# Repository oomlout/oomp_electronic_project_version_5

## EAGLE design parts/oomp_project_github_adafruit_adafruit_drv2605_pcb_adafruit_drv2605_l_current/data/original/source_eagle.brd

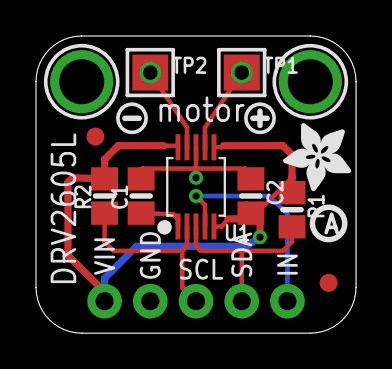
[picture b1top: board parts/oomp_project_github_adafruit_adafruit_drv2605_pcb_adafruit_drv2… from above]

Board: 2 copper layers, 17.8 x 16.5 mm, 16 parts (0 on the bottom side), 8 nets.

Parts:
C1, C2: 1uF; 0805-NO
FID1, FID2: FIDUCIAL""; FIDUCIAL_1MM
JP1: 1X05_ROUND_FULL_76
R1, R2: 10K; 0805-NO
TP1, TP2: TESTPOINT_PAD_2MM
U1: DRV2605LDGS; PSOP10
U$2, U$3: MOUNTINGHOLE2.5; MOUNTINGHOLE_2.5_PLATED
U$4: SYMBOL_PLUS
U$5: SYMBOL_MINUS
U$15: PCBFEAT-REV-040
U$18: ADAFRUIT_3.5MM

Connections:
GND: C1.1, C2.2, JP1.2, U1.8
IN/TRIG: JP1.5, U1.4
unnamed: C1.2, U1.1
OUT+: TP1.P$1, U1.7
OUT-: TP2.P$1, U1.9
SCL: JP1.3, R2.1, U1.2
SDA: JP1.4, R1.1, U1.3
VIN: C2.1, JP1.1, R1.2, R2.2, U1.5, U1.6, U1.10

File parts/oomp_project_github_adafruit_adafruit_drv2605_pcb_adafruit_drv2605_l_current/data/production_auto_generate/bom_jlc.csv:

Comment,Designator,Footprint,LCSC Part #
,JP1,Adafruit DRV2605L-import-fps:1X05_ROUND_FULL_76,C42431835
,U$18,Adafruit DRV2605L-import-fps:ADAFRUIT_3.5MM,
,U$15,Adafruit DRV2605L-import-fps:PCBFEAT-REV-040,
,U$5,Adafruit DRV2605L-import-fps:SYMBOL_MINUS,
,U$4,Adafruit DRV2605L-import-fps:SYMBOL_PLUS,
,"TP1,TP2",Adafruit DRV2605L-import-fps:TESTPOINT_PAD_2MM,
10K,"R1,R2",Adafruit DRV2605L-import-fps:0805-NO,C17414
1uF,"C1,C2",Adafruit DRV2605L-import-fps:0805-NO,
DRV2605LDGS,U1,Adafruit DRV2605L-import-fps:PSOP10,

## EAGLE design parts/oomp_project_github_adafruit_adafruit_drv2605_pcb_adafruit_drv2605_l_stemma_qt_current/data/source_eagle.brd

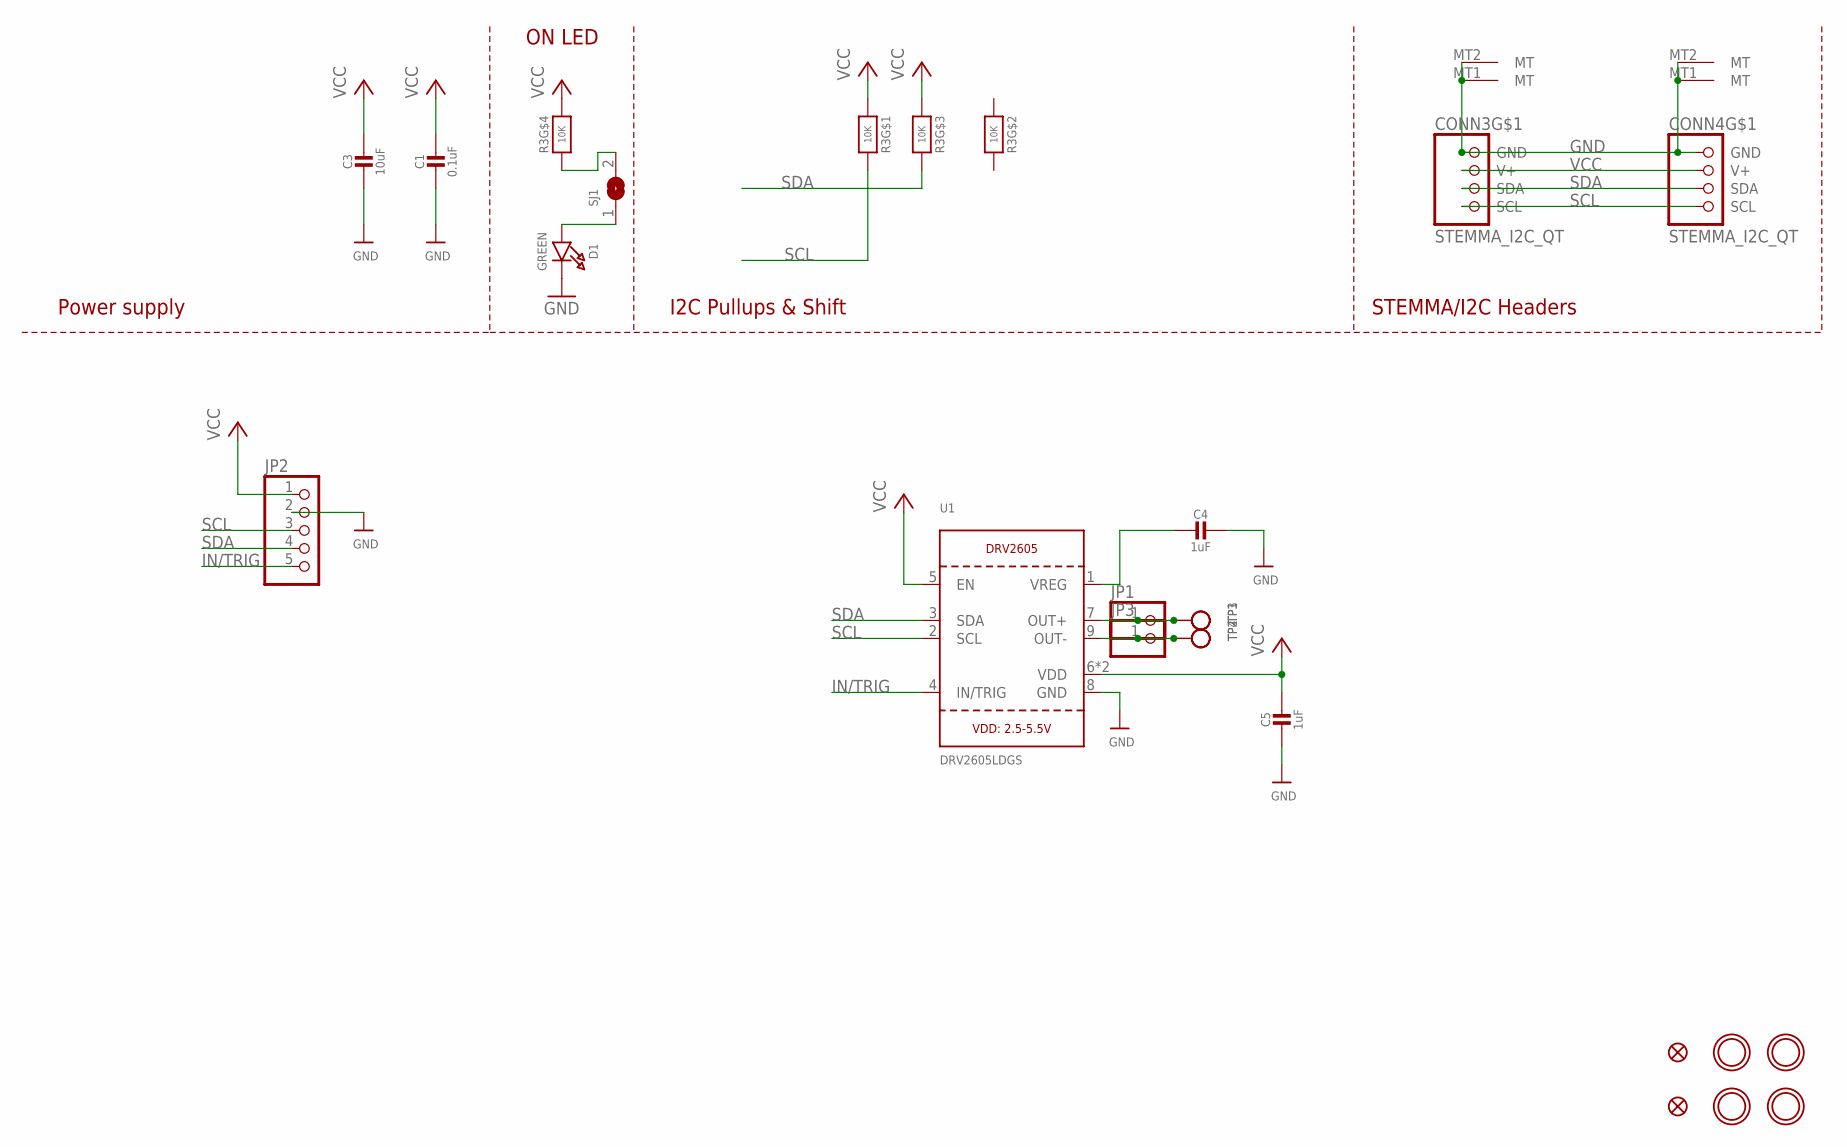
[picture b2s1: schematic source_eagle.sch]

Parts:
C1: 0.1uF; 0603-NO
C3: 10uF; 0805-NO
C4, C5: 1uF; 0603-NO
CONN3, CONN4: STEMMA_I2C_QT; JST_SH4
D1: GREEN; CHIPLED_0603_NOOUTLINE
FID3, FID4: FIDUCIAL_1MM
JP1, JP3: HEADER-1X1; 1X01_OVAL
JP2: HEADER-1X576MIL; 1X05_ROUND_76
R3: 10K; RESPACK_4X0603
SJ1: SOLDERJUMPERCLOSED; SOLDERJUMPER_CLOSEDWIRE
TP1, TP2, TP3, TP4: TESTPOINTPAD2MM; TESTPOINT_PAD_2MM
U1: DRV2605LDGS; PSOP10
U$1, U$17, U$19, U$21: MOUNTINGHOLE2.5; MOUNTINGHOLE_2.5_PLATED

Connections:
GND: C1.2, C3.2, C4.1, C5.2, CONN3.1 (GND), CONN3.MT1 (MT), CONN3.MT2 (MT), CONN4.1 (GND), CONN4.MT1 (MT), CONN4.MT2 (MT), D1.C, JP2.2, U1.8 (GND)
IN/TRIG: JP2.5, U1.4 (IN/TRIG)
unnamed: R3.4 (1), SJ1.2
unnamed: D1.A, SJ1.1
unnamed: C4.2, U1.1 (VREG)
OUT+: JP1.1, TP1.P$1, TP3.P$1, U1.7 (OUT+)
OUT-: JP3.1, TP2.P$1, TP4.P$1, U1.9 (OUT-)
SCL: CONN3.4 (SCL), CONN4.4 (SCL), JP2.3, R3.8 (2), U1.2 (SCL)
SDA: CONN3.3 (SDA), CONN4.3 (SDA), JP2.4, R3.6 (2), U1.3 (SDA)
VCC: C1.1, C3.1, C5.1, CONN3.2 (V+), CONN4.2 (V+), JP2.1, R3.1, R3.3 (1), R3.5 (2), U1.5 (EN), U1.6 (VDD), U1.10 (VDD)

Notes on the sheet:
I2C Pullups & Shift
STEMMA/I2C Headers
ON LED
Power supply

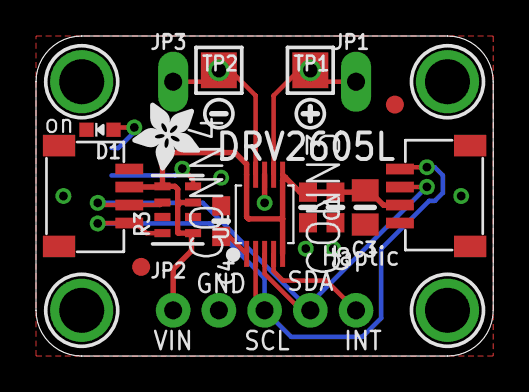
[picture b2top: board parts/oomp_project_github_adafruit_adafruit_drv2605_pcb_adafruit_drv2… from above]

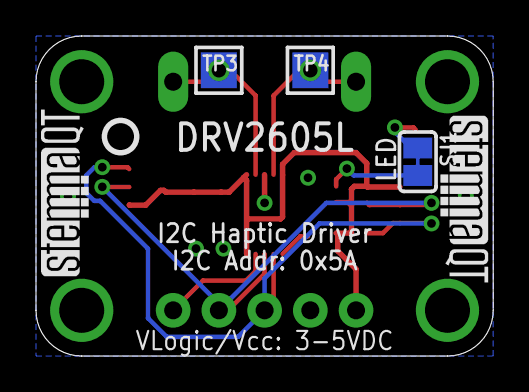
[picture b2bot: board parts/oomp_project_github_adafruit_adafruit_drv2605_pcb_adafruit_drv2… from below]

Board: 2 copper layers, 25.4 x 17.8 mm, 29 parts (6 on the bottom side), 10 nets.

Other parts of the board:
U$2: SYMBOL_PLUS
U$3: SYMBOL_MINUS
U$22: ADAFRUIT_3.5MM
U$25: PCBFEAT-REV-040
U$30, U$31: STEMMAQT

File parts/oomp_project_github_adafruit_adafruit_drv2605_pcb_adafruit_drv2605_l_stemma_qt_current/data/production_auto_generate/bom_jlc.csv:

Comment,Designator,Footprint,LCSC Part #
,"JP1,JP3",Adafruit DRV2605L STEMMA QT-import-fps:1X01_OVAL,C7501259
,JP2,Adafruit DRV2605L STEMMA QT-import-fps:1X05_ROUND_76,C42431835
,U$22,Adafruit DRV2605L STEMMA QT-import-fps:ADAFRUIT_3.5MM,
,U$25,Adafruit DRV2605L STEMMA QT-import-fps:PCBFEAT-REV-040,
,"U$30,U$31",Adafruit DRV2605L STEMMA QT-import-fps:STEMMAQT,
,U$3,Adafruit DRV2605L STEMMA QT-import-fps:SYMBOL_MINUS,
,U$2,Adafruit DRV2605L STEMMA QT-import-fps:SYMBOL_PLUS,
,"TP1,TP2,TP3,TP4",Adafruit DRV2605L STEMMA QT-import-fps:TESTPOINT_PAD_2MM,
0.1uF,C1,Adafruit DRV2605L STEMMA QT-import-fps:0603-NO,C14663
10K,R3,Adafruit DRV2605L STEMMA QT-import-fps:RESPACK_4X0603,C98220
10uF,C3,Adafruit DRV2605L STEMMA QT-import-fps:0805-NO,
1uF,"C4,C5",Adafruit DRV2605L STEMMA QT-import-fps:0603-NO,C5673
DRV2605LDGS,U1,Adafruit DRV2605L STEMMA QT-import-fps:PSOP10,
GREEN,D1,Adafruit DRV2605L STEMMA QT-import-fps:CHIPLED_0603_NOOUTLINE,
STEMMA_I2C_QT,"CONN3,CONN4",Adafruit DRV2605L STEMMA QT-import-fps:JST_SH4,C160404

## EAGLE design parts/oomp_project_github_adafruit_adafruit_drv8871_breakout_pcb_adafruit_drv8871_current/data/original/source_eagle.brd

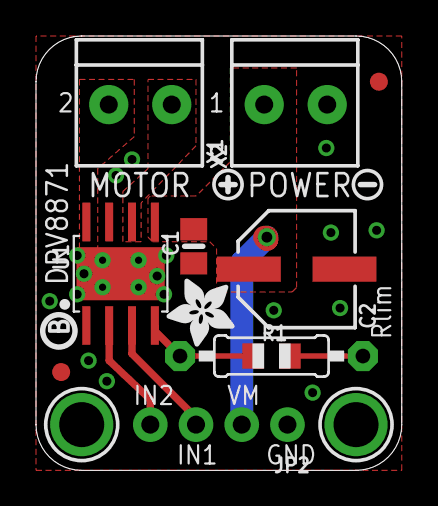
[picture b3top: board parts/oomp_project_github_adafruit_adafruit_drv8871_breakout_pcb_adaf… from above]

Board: 2 copper layers, 20.3 x 24.1 mm, 15 parts (0 on the bottom side), 7 nets.

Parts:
C1: 0.1uF/50V; 0805-NO
C2: 22uF/63V; PANASONIC_D
FID1, FID2: FIDUCIAL""; FIDUCIAL_1MM
JP2: 1X04_ROUND_76
R1: 30K; 0805-THM
U1: DRV8871; HSOP8
U$9, U$10: MOUNTINGHOLE2.5; MOUNTINGHOLE_2.5_PLATED
U$11: SYMBOL_PLUS
U$12: SYMBOL_MINUS
U$14: ADAFRUIT_3.5MM
U$15: PCBFEAT-REV-040
X1: DCMOTOR; TERMBLOCK_1X2-3.5MM
X2: POWER; TERMBLOCK_1X2-3.5MM

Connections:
GND: C1.2, C2.-, JP2.1, R1.1, U1.1, U1.7, U1.GND, U1.P$1, U1.P$2, U1.P$3, U1.P$4, X2.2
IN1: JP2.3, U1.3
IN2: JP2.4, U1.2
unnamed: R1.2, U1.4
OUT1: U1.6, X1.2
OUT2: U1.8, X1.1
VMOTOR: C1.1, C2.+, JP2.2, U1.5, X2.1

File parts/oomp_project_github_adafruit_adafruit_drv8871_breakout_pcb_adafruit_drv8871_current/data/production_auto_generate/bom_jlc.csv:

Comment,Designator,Footprint,LCSC Part #
,JP2,Adafruit DRV8871-import-fps:1X04_ROUND_76,C42431795
,U$14,Adafruit DRV8871-import-fps:ADAFRUIT_3.5MM,
,U$15,Adafruit DRV8871-import-fps:PCBFEAT-REV-040,
,U$12,Adafruit DRV8871-import-fps:SYMBOL_MINUS,
,U$11,Adafruit DRV8871-import-fps:SYMBOL_PLUS,
0.1uF/50V,C1,Adafruit DRV8871-import-fps:0805-NO,
22uF/63V,C2,Adafruit DRV8871-import-fps:PANASONIC_D,
30K,R1,Adafruit DRV8871-import-fps:0805-THM,
DCMOTOR,X1,Adafruit DRV8871-import-fps:TERMBLOCK_1X2-3.5MM,
DRV8871,U1,Adafruit DRV8871-import-fps:HSOP8,
POWER,X2,Adafruit DRV8871-import-fps:TERMBLOCK_1X2-3.5MM,

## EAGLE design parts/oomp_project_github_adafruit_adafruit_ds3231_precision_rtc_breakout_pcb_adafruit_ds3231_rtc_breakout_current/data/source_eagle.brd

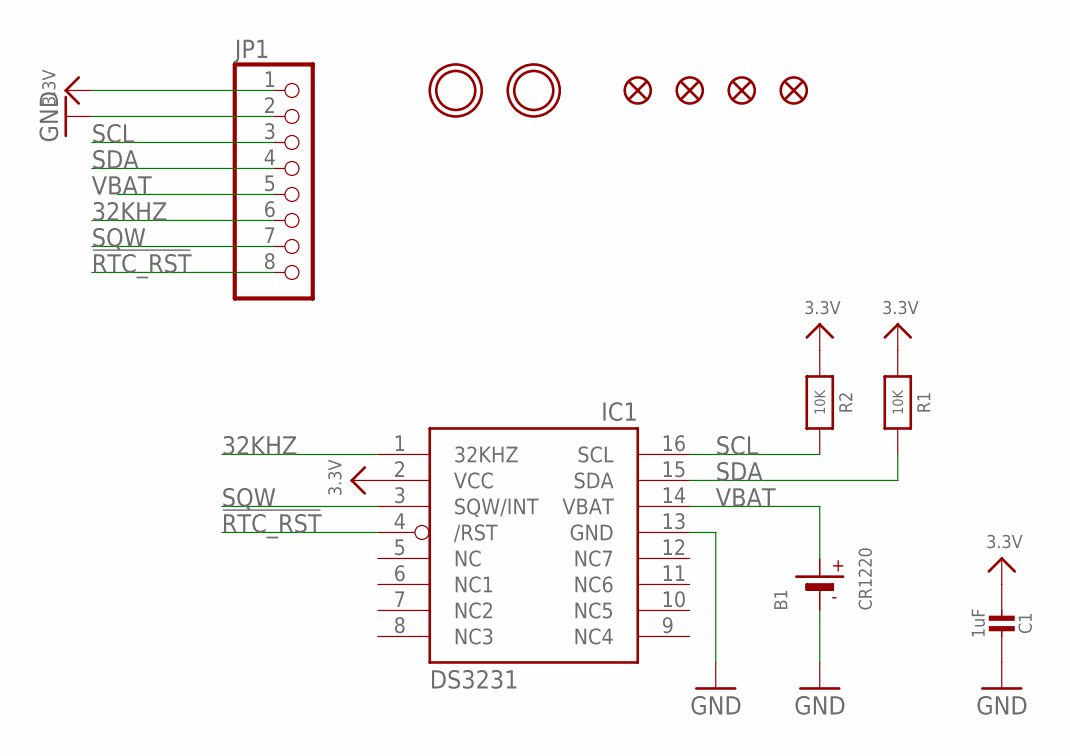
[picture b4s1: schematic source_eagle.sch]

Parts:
B1: CR1220
C1: 1uF; 0805-NO
FID1, FID2, FID3, FID4: FIDUCIAL""; FIDUCIAL_1MM
IC1: DS3231/SO; SO16W
JP1: HEADER-1X870MIL; 1X08_ROUND_70
R1, R2: 10K; 0805-NO
U$6, U$7: MOUNTINGHOLE2.5; MOUNTINGHOLE_2.5_PLATED

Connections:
3.3V: C1.2, IC1.2 (VCC), JP1.1, R1.1, R2.1
32KHZ: IC1.1 (32KHZ), JP1.6
!RTC_RST: IC1.4 (/RST), JP1.8
GND: B1.-, C1.1, IC1.13 (GND), JP1.2
SCL: IC1.16 (SCL), JP1.3, R2.2
SDA: IC1.15 (SDA), JP1.4, R1.2
SQW: IC1.3 (SQW/INT), JP1.7
VBAT: B1.+$1 (+), IC1.14 (VBAT), JP1.5

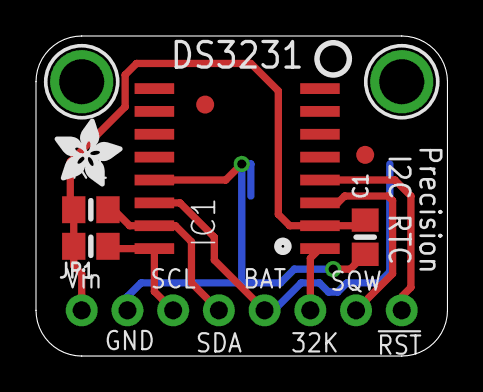
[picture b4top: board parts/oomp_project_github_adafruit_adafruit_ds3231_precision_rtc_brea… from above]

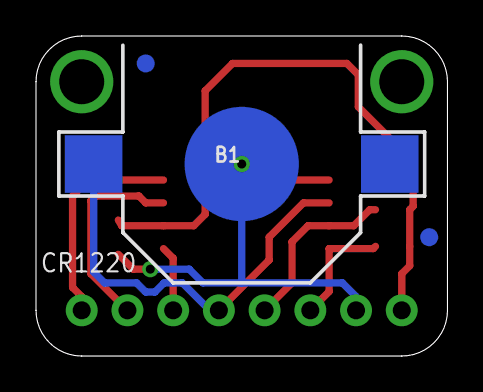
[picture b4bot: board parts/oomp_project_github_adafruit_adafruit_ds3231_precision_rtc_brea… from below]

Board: 2 copper layers, 22.9 x 17.8 mm, 14 parts (3 on the bottom side), 8 nets.

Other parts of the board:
U$8: ADAFRUIT_3.5MM
U$9: PCBFEAT-REV-040

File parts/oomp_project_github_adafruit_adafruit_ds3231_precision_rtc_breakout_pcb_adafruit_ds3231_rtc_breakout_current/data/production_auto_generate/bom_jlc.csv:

Comment,Designator,Footprint,LCSC Part #
,JP1,Adafruit DS3231 RTC Breakout-import-fps:1X08_ROUND_70,C492421
,U$8,Adafruit DS3231 RTC Breakout-import-fps:ADAFRUIT_3.5MM,
,U$9,Adafruit DS3231 RTC Breakout-import-fps:PCBFEAT-REV-040,
10K,"R1,R2",Adafruit DS3231 RTC Breakout-import-fps:0805-NO,C17414
1uF,C1,Adafruit DS3231 RTC Breakout-import-fps:0805-NO,
CR1220,B1,Adafruit DS3231 RTC Breakout-import-fps:CR1220,
DS3231/SO,IC1,Adafruit DS3231 RTC Breakout-import-fps:SO16W,

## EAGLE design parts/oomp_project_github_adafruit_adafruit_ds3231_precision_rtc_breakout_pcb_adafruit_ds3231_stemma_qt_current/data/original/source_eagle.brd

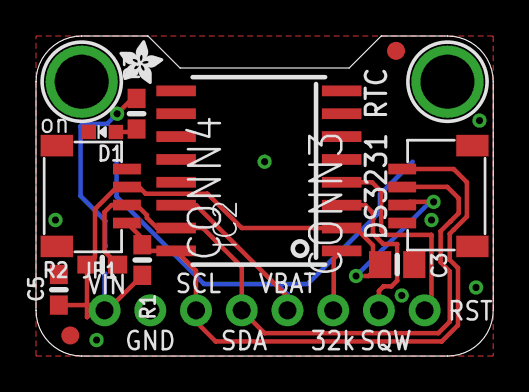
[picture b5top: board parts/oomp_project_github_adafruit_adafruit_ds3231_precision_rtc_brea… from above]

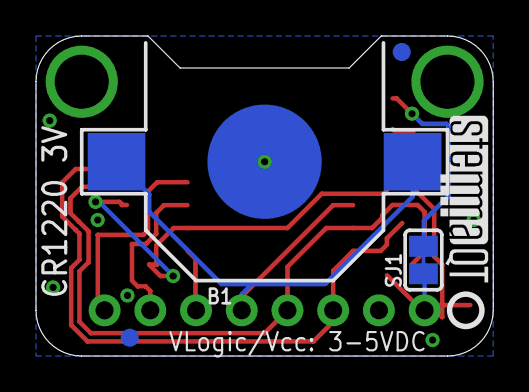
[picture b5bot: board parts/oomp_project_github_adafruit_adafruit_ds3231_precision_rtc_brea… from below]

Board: 2 copper layers, 25.4 x 17.8 mm, 21 parts (6 on the bottom side), 10 nets.

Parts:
B1: CR1220
C3: 10uF; 0805-NO
C5: 0.1uF; 0603-NO
CONN3, CONN4: STEMMA_I2C_QT; JST_SH4
D1: GREEN; CHIPLED_0603_NOOUTLINE
FID1, FID2, FID3, FID4: FIDUCIAL_1MM
IC2: DS3231/SO; SO16W
JP1: 1X08_ROUND_70
R1, R2, R3: 10k; 0603-NO
SJ1: SOLDERJUMPER_CLOSEDWIRE
U$1: ADAFRUIT_2.5MM
U$9, U$17: MOUNTINGHOLE3.0THIN; MOUNTINGHOLE_3.0_PLATEDTHIN
U$25: PCBFEAT-REV-040
U$31: STEMMAQT

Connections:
32KHZ: IC2.1, JP1.6
!RTC_RST: IC2.4, JP1.8
GND: B1.-, C3.2, C5.2, CONN3.1, CONN3.MT1, CONN3.MT2, CONN4.1, CONN4.MT1, CONN4.MT2, D1.C, IC2.5, IC2.6, IC2.7, IC2.8, IC2.9, IC2.10, IC2.11, IC2.12, IC2.13, JP1.2
unnamed: R3.2, SJ1.2
unnamed: D1.A, R3.1
SCL: CONN3.4, CONN4.4, IC2.16, JP1.3, R1.1
SDA: CONN3.3, CONN4.3, IC2.15, JP1.4, R2.1
SQW: IC2.3, JP1.7
VBAT: B1.+$1, B1.+$2, IC2.14, JP1.5
VCC: C3.1, C5.1, CONN3.2, CONN4.2, IC2.2, JP1.1, R1.2, R2.2, SJ1.1

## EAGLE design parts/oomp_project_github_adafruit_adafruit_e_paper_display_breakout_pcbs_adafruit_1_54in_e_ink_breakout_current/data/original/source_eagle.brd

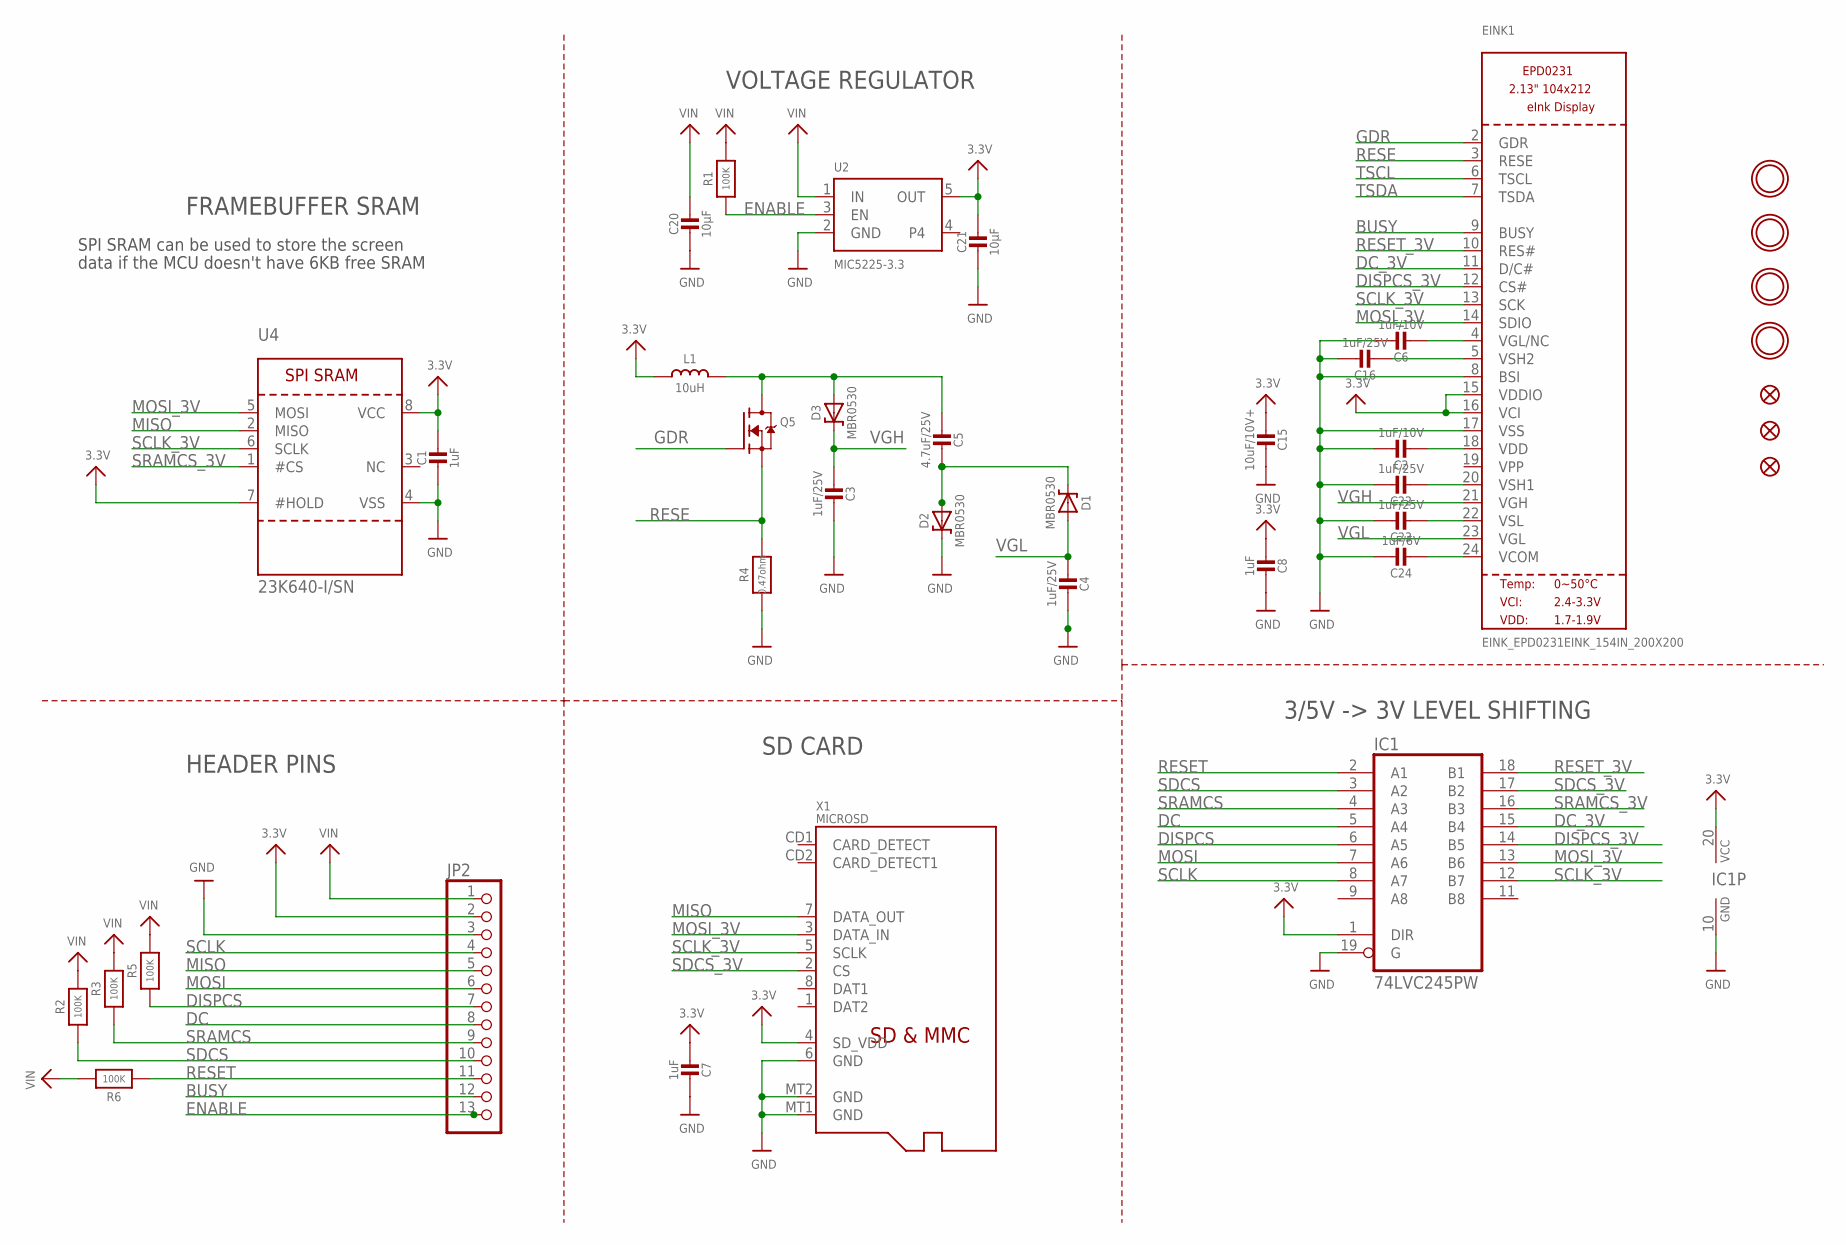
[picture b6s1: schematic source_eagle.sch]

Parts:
C1: 1uF; 0805_10MGAP
C2, C6: 1uF/10V; 0805-NO
C3, C4, C16, C22, C23: 1uF/25V; 0805-NO
C5: 4.7uF/25V; 0805-NO
C7, C8: 1uF; 0805-NO
C15: 10uF/10V+; 0805-NO
C20, C21: 10µF; 0805-NO
C24: 1uF/6V; 0805-NO
D1, D2, D3: MBR0530; SOD-123
EINK1: EINK_EPD0231EINK_154IN_200X200; EINK_154IN
FID1, FID2, FID3: FIDUCIAL_1MM
IC1: 74LVC245PW; TSSOP20
JP2: HEADER-1X13; 1X13_ROUND_70
L1: 10uH; INDUCTOR_4X4MM_NR401
Q5: IRLML0100; SOT23-3
R1, R2, R3, R5, R6: 100K; 0805-NO
R4: 0.47ohm; 0805_10MGAP
U2: MIC5225-3.3; SOT23-5
U4: 23K640-I/SN; SOIC8_150MIL
U$3, U$4, U$5, U$6: MOUNTINGHOLE2.5; MOUNTINGHOLE_2.5_PLATED
X1: MICROSD

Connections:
3.3V: C1.1, C7.1, C8.1, C15.2, C21.1, EINK1.15 (VDDIO), EINK1.16 (VCI), IC1.1 (DIR), IC1.20 (VCC), JP2.2, L1.P$2 (2), U2.5 (OUT), U4.7 (#HOLD), U4.8 (VCC), X1.4 (SD_VDD)
BUSY: EINK1.9 (BUSY), JP2.12
DC: IC1.5 (A4), JP2.8
DC_3V: EINK1.11 (D/C#), IC1.15 (B4)
DISPCS: IC1.6 (A5), JP2.7, R5.1
DISPCS_3V: EINK1.12 (CS#), IC1.14 (B5)
ENABLE: JP2.13, R1.1, U2.3 (EN)
GDR: EINK1.2 (GDR), Q5.1 (G)
GND: C1.2, C2.1, C3.2, C4.2, C6.1, C7.2, C8.2, C15.1, C16.1, C20.2, C21.2, C22.1, C23.1, C24.1, D2.C, EINK1.8 (BSI), EINK1.17 (VSS), IC1.10 (GND), IC1.19 (G), JP2.3, R4.2, U2.2 (GND), U4.4 (VSS), X1.6 (GND), X1.MT1 (GND), X1.MT2 (GND)
MISO: JP2.5, U4.2 (MISO), X1.7 (DATA_OUT)
MOSI: IC1.7 (A6), JP2.6
MOSI_3V: EINK1.14 (SDIO), IC1.13 (B6), U4.5 (MOSI), X1.3 (DATA_IN)
unnamed: C5.2, D1.C, D2.A
unnamed: C5.1, D3.A, L1.P$1 (1), Q5.3 (D)
unnamed: C16.2, EINK1.5 (VSH2)
unnamed: C2.2, EINK1.18 (VDD)
unnamed: C22.2, EINK1.20 (VSH1)
unnamed: C6.2, EINK1.4 (VGL/NC)
unnamed: C23.2, EINK1.22 (VSL)
unnamed: C24.2, EINK1.24 (VCOM)
RESE: EINK1.3 (RESE), Q5.2 (S), R4.1
RESET: IC1.2 (A1), JP2.11, R6.1
RESET_3V: EINK1.10 (RES#), IC1.18 (B1)
SCLK: IC1.8 (A7), JP2.4
SCLK_3V: EINK1.13 (SCK), IC1.12 (B7), U4.6 (SCLK), X1.5 (SCLK)
SDCS: IC1.3 (A2), JP2.10, R2.1
SDCS_3V: IC1.17 (B2), X1.2 (CS)
SRAMCS: IC1.4 (A3), JP2.9, R3.1
SRAMCS_3V: IC1.16 (B3), U4.1 (#CS)
TSCL: EINK1.6 (TSCL)
TSDA: EINK1.7 (TSDA)
VGH: C3.1, D3.C, EINK1.21 (VGH)
VGL: C4.1, D1.A, EINK1.23 (VGL)
VIN: C20.1, JP2.1, R1.2, R2.2, R3.2, R5.2, R6.2, U2.1 (IN)

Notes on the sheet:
VOLTAGE REGULATOR
3/5V -> 3V LEVEL SHIFTING
HEADER PINS
FRAMEBUFFER SRAM
SPI SRAM can be used to store the screen
data if the MCU doesn't have 6KB free SRAM
SD CARD

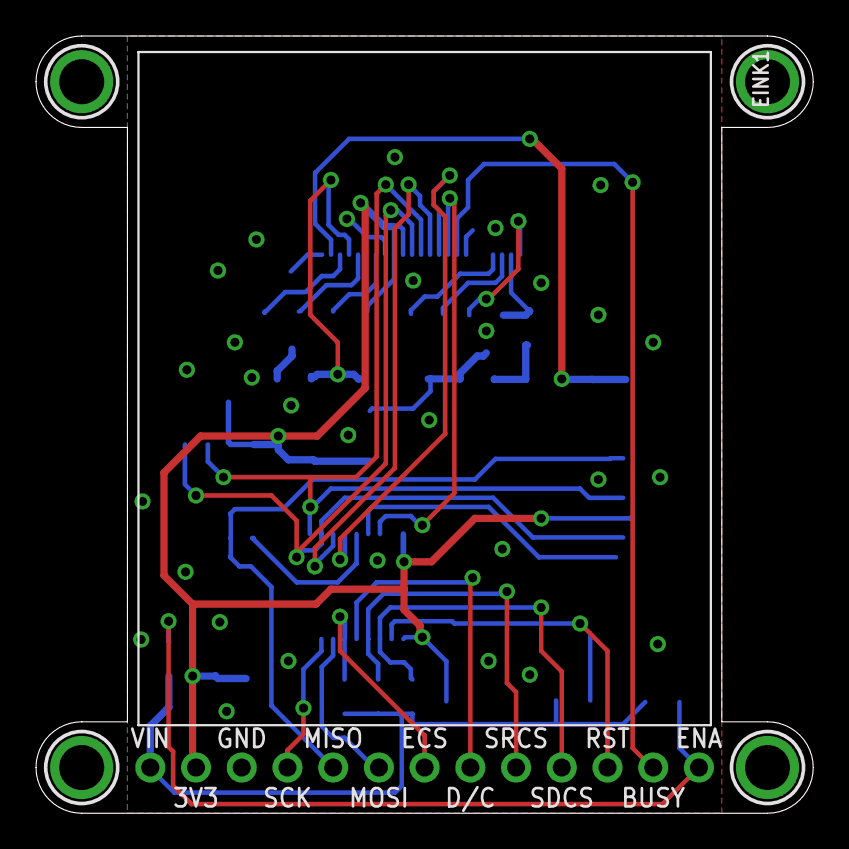
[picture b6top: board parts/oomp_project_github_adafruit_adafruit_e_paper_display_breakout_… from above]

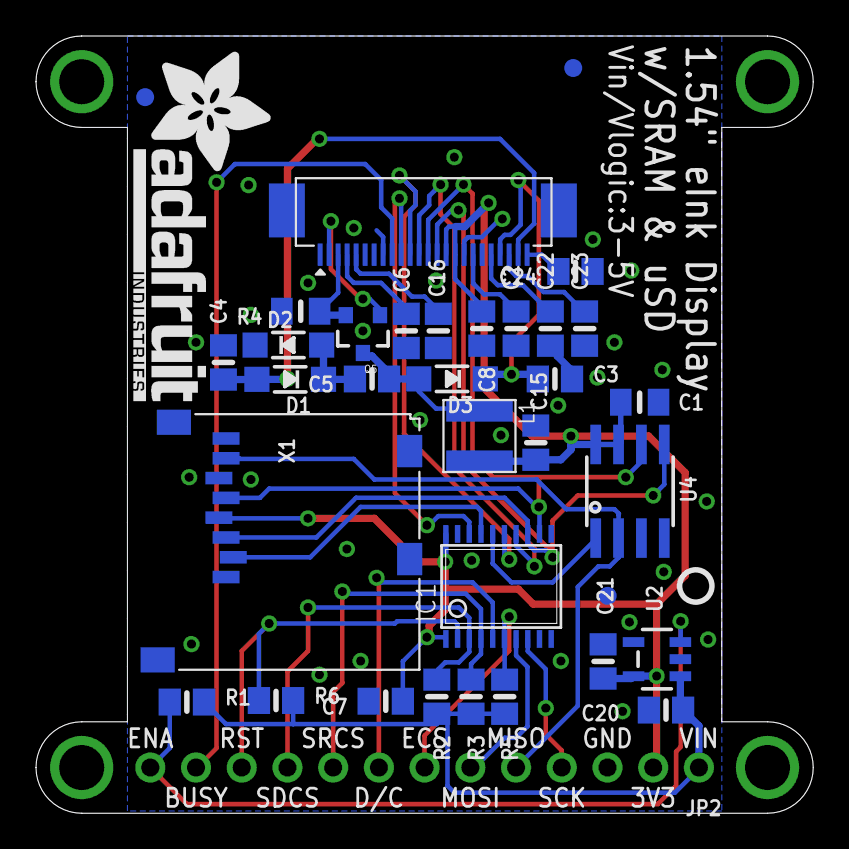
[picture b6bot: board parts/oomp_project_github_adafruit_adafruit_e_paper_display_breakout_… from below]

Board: 2 copper layers, 43.2 x 43.2 mm, 41 parts (36 on the bottom side), 32 nets.

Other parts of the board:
U$9: PCBFEAT-REV-040
U$28: ADAFRUIT_TEXT_20MM

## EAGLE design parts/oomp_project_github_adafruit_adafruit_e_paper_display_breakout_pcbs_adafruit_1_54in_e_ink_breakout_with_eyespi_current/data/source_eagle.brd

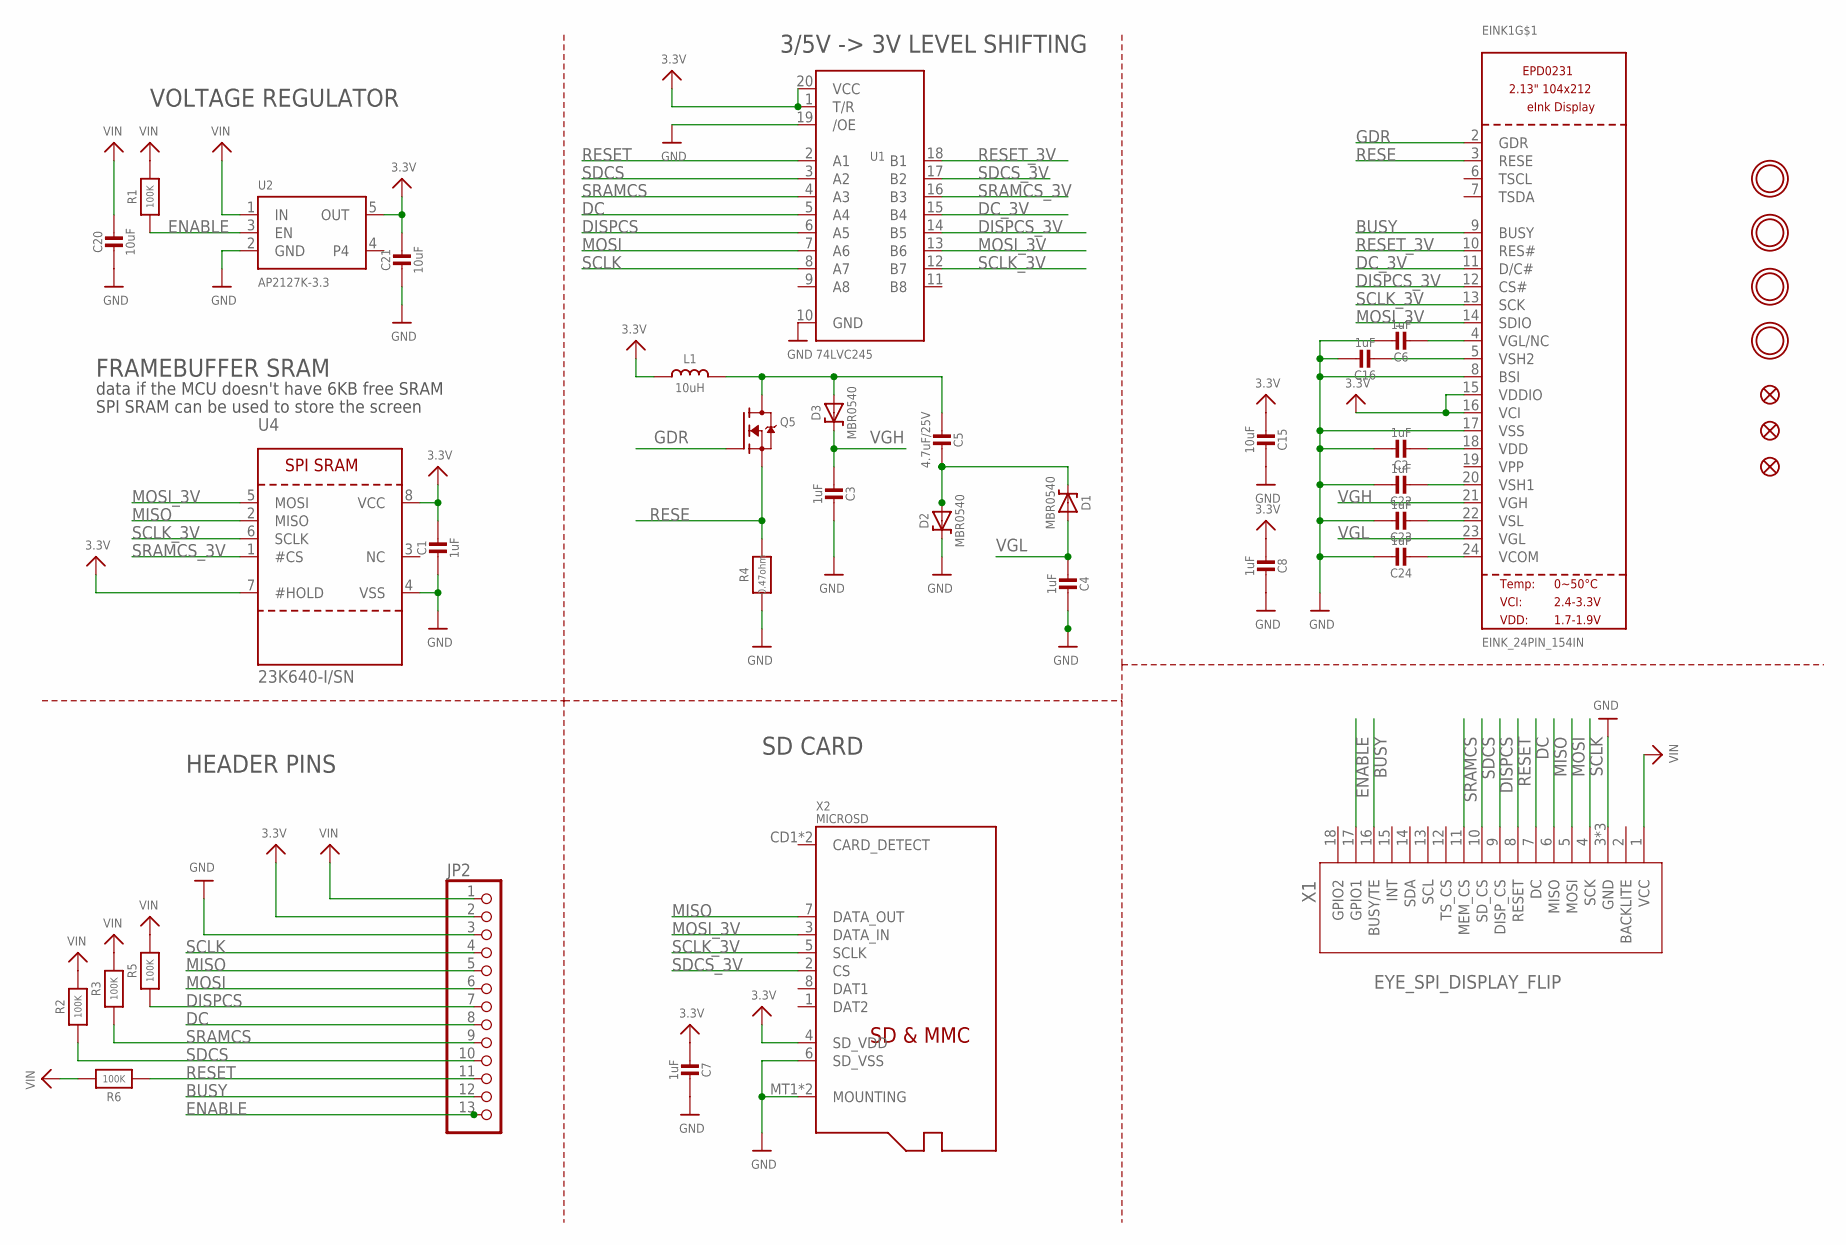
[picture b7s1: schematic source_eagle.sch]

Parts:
C1, C2, C3, C4, C6, C7, C8, C16, C22, C23, C24: 1uF; 0805-NO
C5: 4.7uF/25V; 0805-NO
C15, C20, C21: 10uF; 0805-NO
D1, D2, D3: MBR0540; SOD-123
EINK1: EINK_24PIN_154IN; EINK_154IN
FID1, FID2, FID3: FIDUCIAL_1MM
JP2: HEADER-1X13; 1X13_ROUND_70
L1: 10uH; INDUCTOR_4X4MM_NR401
Q5: IRLML0100; SOT23-3
R1, R2, R3, R5, R6: 100K; 0805-NO
R4: 0.47ohm; 0805_10MGAP
U1: 74LVC245; TSSOP20
U2: AP2127K-3.3; SOT23-5
U4: 23K640-I/SN; SOIC8_150MIL
U$3, U$4, U$5, U$6: MOUNTINGHOLE2.5; MOUNTINGHOLE_2.5_PLATED
X1: EYE_SPI_DISPLAY_FLIP; EYE_SPI_DISPLAY_BOTCONTACT
X2: MICROSD

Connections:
3.3V: C1.1, C7.1, C8.1, C15.2, C21.1, EINK1.15 (VDDIO), EINK1.16 (VCI), JP2.2, L1.P$2 (2), U1.1 (T/R), U1.20 (VCC), U2.5 (OUT), U4.7 (#HOLD), U4.8 (VCC), X2.4 (SD_VDD)
BUSY: EINK1.9 (BUSY), JP2.12, X1.16 (BUSY/TE)
DC: JP2.8, U1.5 (A4), X1.7 (DC)
DC_3V: EINK1.11 (D/C#), U1.15 (B4)
DISPCS: JP2.7, R5.1, U1.6 (A5), X1.9 (DISP_CS)
DISPCS_3V: EINK1.12 (CS#), U1.14 (B5)
ENABLE: JP2.13, R1.1, U2.3 (EN), X1.17 (GPIO1)
GDR: EINK1.2 (GDR), Q5.1 (G)
GND: C1.2, C2.1, C3.2, C4.2, C6.1, C7.2, C8.2, C15.1, C16.1, C20.2, C21.2, C22.1, C23.1, C24.1, D2.C, EINK1.8 (BSI), EINK1.17 (VSS), JP2.3, R4.2, U1.10 (GND), U1.19 (/OE), U2.2 (GND), U4.4 (VSS), X1.3 (GND), X1.SUPPORT1 (GND), X1.SUPPORT2 (GND), X2.6 (SD_VSS), X2.MT1 (MOUNTING), X2.MT2 (MOUNTING)
MISO: JP2.5, U4.2 (MISO), X1.6 (MISO), X2.7 (DATA_OUT)
MOSI: JP2.6, U1.7 (A6), X1.5 (MOSI)
MOSI_3V: EINK1.14 (SDIO), U1.13 (B6), U4.5 (MOSI), X2.3 (DATA_IN)
unnamed: C5.2, D1.C, D2.A
unnamed: C5.1, D3.A, L1.P$1 (1), Q5.3 (D)
unnamed: C16.2, EINK1.5 (VSH2)
unnamed: C2.2, EINK1.18 (VDD)
unnamed: C22.2, EINK1.20 (VSH1)
unnamed: C6.2, EINK1.4 (VGL/NC)
unnamed: C23.2, EINK1.22 (VSL)
unnamed: C24.2, EINK1.24 (VCOM)
RESE: EINK1.3 (RESE), Q5.2 (S), R4.1
RESET: JP2.11, R6.1, U1.2 (A1), X1.8 (RESET)
RESET_3V: EINK1.10 (RES#), U1.18 (B1)
SCLK: JP2.4, U1.8 (A7), X1.4 (SCK)
SCLK_3V: EINK1.13 (SCK), U1.12 (B7), U4.6 (SCLK), X2.5 (SCLK)
SDCS: JP2.10, R2.1, U1.3 (A2), X1.10 (SD_CS)
SDCS_3V: U1.17 (B2), X2.2 (CS)
SRAMCS: JP2.9, R3.1, U1.4 (A3), X1.11 (MEM_CS)
SRAMCS_3V: U1.16 (B3), U4.1 (#CS)
VGH: C3.1, D3.C, EINK1.21 (VGH)
VGL: C4.1, D1.A, EINK1.23 (VGL)
VIN: C20.1, JP2.1, R1.2, R2.2, R3.2, R5.2, R6.2, U2.1 (IN), X1.1 (VCC)

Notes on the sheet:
VOLTAGE REGULATOR
3/5V -> 3V LEVEL SHIFTING
HEADER PINS
FRAMEBUFFER SRAM
SPI SRAM can be used to store the screen
data if the MCU doesn't have 6KB free SRAM
SD CARD

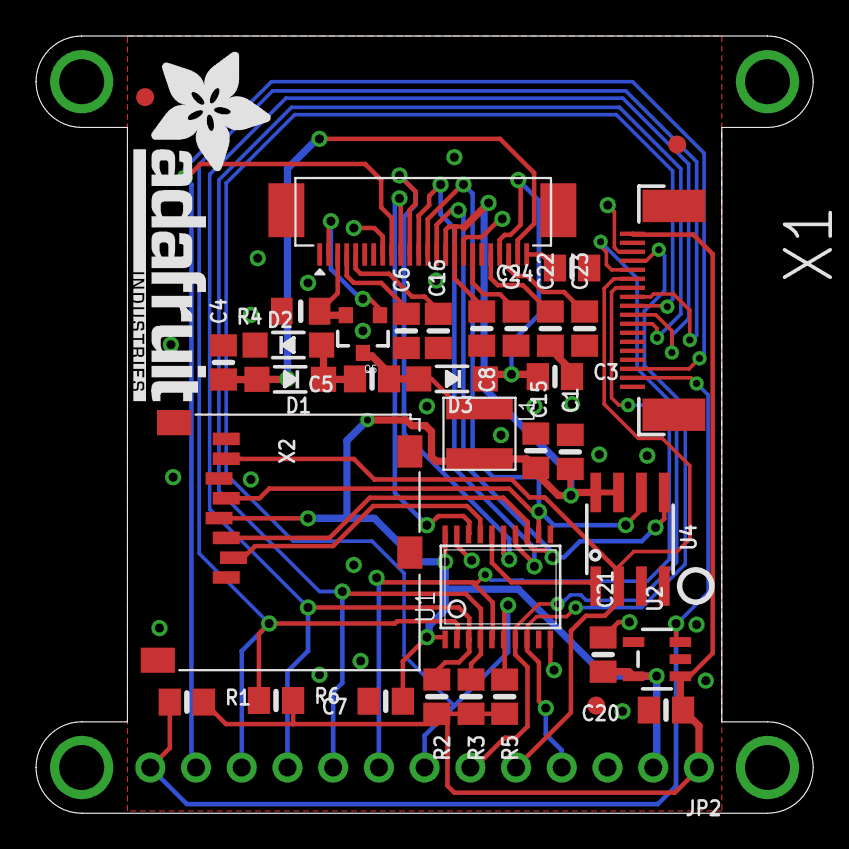
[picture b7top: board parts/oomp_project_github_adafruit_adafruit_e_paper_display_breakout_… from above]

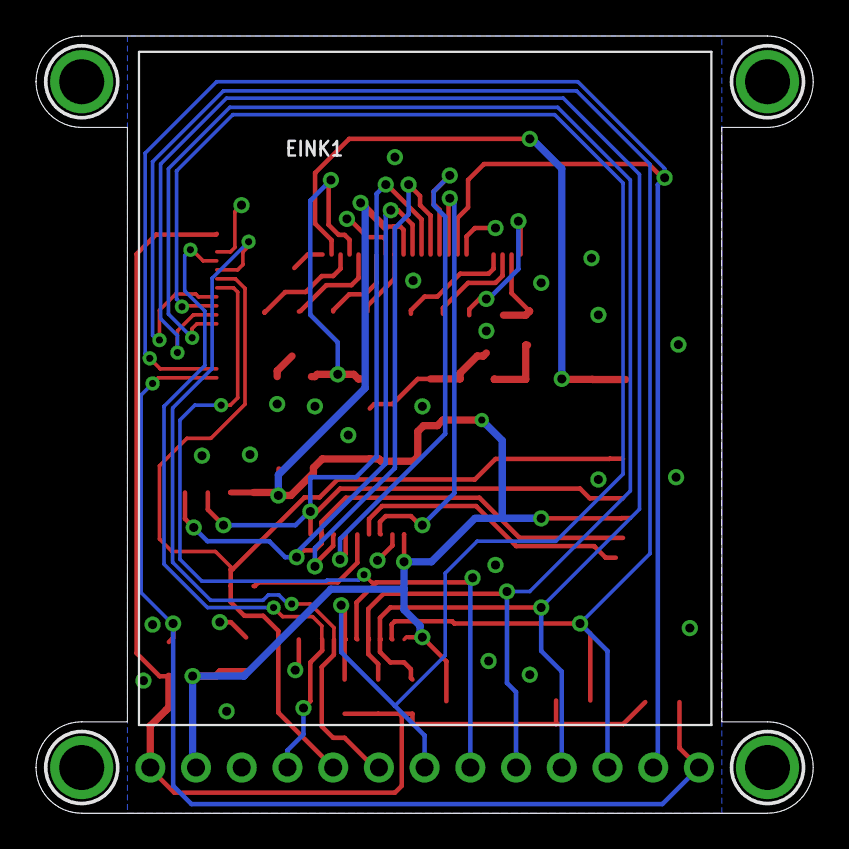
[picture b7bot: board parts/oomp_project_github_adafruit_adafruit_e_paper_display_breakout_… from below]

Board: 2 copper layers, 43.2 x 43.2 mm, 70 parts (18 on the bottom side), 32 nets.

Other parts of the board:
PLABEL0: PLABEL0
PLABEL1: PLABEL1
PLABEL2: PLABEL2
PLABEL3: PLABEL3
PLABEL4: PLABEL4
PLABEL5: PLABEL5
PLABEL6: PLABEL6
PLABEL7: PLABEL7
PLABEL8: PLABEL8
PLABEL9: PLABEL9
PLABEL10: PLABEL10
PLABEL11: PLABEL11
PLABEL12: PLABEL12
PLABEL13: PLABEL13
PLABEL14: PLABEL14
PLABEL15: PLABEL15
PLABEL16: PLABEL16
PLABEL17: PLABEL17
PLABEL18: PLABEL18
PLABEL19: PLABEL19
PLABEL20: PLABEL20
PLABEL21: PLABEL21
PLABEL22: PLABEL22
PLABEL23: PLABEL23
PLABEL24: PLABEL24
PLABEL25: PLABEL25
PLABEL26: PLABEL26
PLABEL27: PLABEL27
U$9: PCBFEAT-REV-040
U$28: ADAFRUIT_TEXT_20MM

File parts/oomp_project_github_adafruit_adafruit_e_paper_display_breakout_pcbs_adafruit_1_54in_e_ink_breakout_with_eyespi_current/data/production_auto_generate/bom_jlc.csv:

Comment,Designator,Footprint,LCSC Part #
,JP2,Adafruit 1.54in eInk Breakout with EYESPI-import-fps:1X13_ROUND_70,C2894936
,U$28,Adafruit 1.54in eInk Breakout with EYESPI-import-fps:ADAFRUIT_TEXT_20MM,
,U$9,Adafruit 1.54in eInk Breakout with EYESPI-import-fps:PCBFEAT-REV-040,
,PLABEL0,Adafruit 1.54in eInk Breakout with EYESPI-import-fps:PLABEL0,
,PLABEL1,Adafruit 1.54in eInk Breakout with EYESPI-import-fps:PLABEL1,
,PLABEL10,Adafruit 1.54in eInk Breakout with EYESPI-import-fps:PLABEL10,
,PLABEL11,Adafruit 1.54in eInk Breakout with EYESPI-import-fps:PLABEL11,
,PLABEL12,Adafruit 1.54in eInk Breakout with EYESPI-import-fps:PLABEL12,
,PLABEL13,Adafruit 1.54in eInk Breakout with EYESPI-import-fps:PLABEL13,
,PLABEL14,Adafruit 1.54in eInk Breakout with EYESPI-import-fps:PLABEL14,
,PLABEL15,Adafruit 1.54in eInk Breakout with EYESPI-import-fps:PLABEL15,
,PLABEL16,Adafruit 1.54in eInk Breakout with EYESPI-import-fps:PLABEL16,
,PLABEL17,Adafruit 1.54in eInk Breakout with EYESPI-import-fps:PLABEL17,
,PLABEL18,Adafruit 1.54in eInk Breakout with EYESPI-import-fps:PLABEL18,
,PLABEL19,Adafruit 1.54in eInk Breakout with EYESPI-import-fps:PLABEL19,
,PLABEL2,Adafruit 1.54in eInk Breakout with EYESPI-import-fps:PLABEL2,
,PLABEL20,Adafruit 1.54in eInk Breakout with EYESPI-import-fps:PLABEL20,
,PLABEL21,Adafruit 1.54in eInk Breakout with EYESPI-import-fps:PLABEL21,
,PLABEL22,Adafruit 1.54in eInk Breakout with EYESPI-import-fps:PLABEL22,
,PLABEL23,Adafruit 1.54in eInk Breakout with EYESPI-import-fps:PLABEL23,
,PLABEL24,Adafruit 1.54in eInk Breakout with EYESPI-import-fps:PLABEL24,
,PLABEL25,Adafruit 1.54in eInk Breakout with EYESPI-import-fps:PLABEL25,
,PLABEL26,Adafruit 1.54in eInk Breakout with EYESPI-import-fps:PLABEL26,
,PLABEL27,Adafruit 1.54in eInk Breakout with EYESPI-import-fps:PLABEL27,
,PLABEL3,Adafruit 1.54in eInk Breakout with EYESPI-import-fps:PLABEL3,
,PLABEL4,Adafruit 1.54in eInk Breakout with EYESPI-import-fps:PLABEL4,
,PLABEL5,Adafruit 1.54in eInk Breakout with EYESPI-import-fps:PLABEL5,
,PLABEL6,Adafruit 1.54in eInk Breakout with EYESPI-import-fps:PLABEL6,
,PLABEL7,Adafruit 1.54in eInk Breakout with EYESPI-import-fps:PLABEL7,
,PLABEL8,Adafruit 1.54in eInk Breakout with EYESPI-import-fps:PLABEL8,
,PLABEL9,Adafruit 1.54in eInk Breakout with EYESPI-import-fps:PLABEL9,
0.47ohm,R4,Adafruit 1.54in eInk Breakout with EYESPI-import-fps:0805_10MGAP,
100K,"R1,R2,R3,R5,R6",Adafruit 1.54in eInk Breakout with EYESPI-import-fps:0805-NO,C149504
10uF,"C15,C20,C21",Adafruit 1.54in eInk Breakout with EYESPI-import-fps:0805-NO,
10uH,L1,Adafruit 1.54in eInk Breakout with EYESPI-import-fps:INDUCTOR_4X4MM_NR401,
1uF,"C1,C2,C3,C4,C6,C7,C8,C16,C22,C23,C24",Adafruit 1.54in eInk Breakout with EYESPI-import-fps:0805-NO,
23K640-I/SN,U4,Adafruit 1.54in eInk Breakout with EYESPI-import-fps:SOIC8_150MIL,
4.7uF/25V,C5,Adafruit 1.54in eInk Breakout with EYESPI-import-fps:0805-NO,
74LVC245,U1,Adafruit 1.54in eInk Breakout with EYESPI-import-fps:TSSOP20,
AP2127K-3.3,U2,Adafruit 1.54in eInk Breakout with EYESPI-import-fps:SOT23-5,
EINK_24PIN_154IN,EINK1,Adafruit 1.54in eInk Breakout with EYESPI-import-fps:EINK_154IN,
EYE_SPI_DISPLAY_FLIP,X1,Adafruit 1.54in eInk Breakout with EYESPI-import-fps:EYE_SPI_DISPLAY_BOTCONTACT,
IRLML0100,Q5,Adafruit 1.54in eInk Breakout with EYESPI-import-fps:SOT23-3,
MBR0540,"D1,D2,D3",Adafruit 1.54in eInk Breakout with EYESPI-import-fps:SOD-123,
MICROSD,X2,Adafruit 1.54in eInk Breakout with EYESPI-import-fps:MICROSD,

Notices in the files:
parts and their libraries:
microbuilder: This work is placed in the public domain, and may be freely used for commercial and non-commercial work with the following conditions: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
